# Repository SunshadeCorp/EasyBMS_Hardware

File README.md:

# EasyBMS_Hardware
PCB of the EasyBMS as an EAGLE project

Used EAGLE default design rules with one modification: under "Masks" in DRC settings, set "Limit" to 20mil to cover vias that have smaller drill size with solder mask.

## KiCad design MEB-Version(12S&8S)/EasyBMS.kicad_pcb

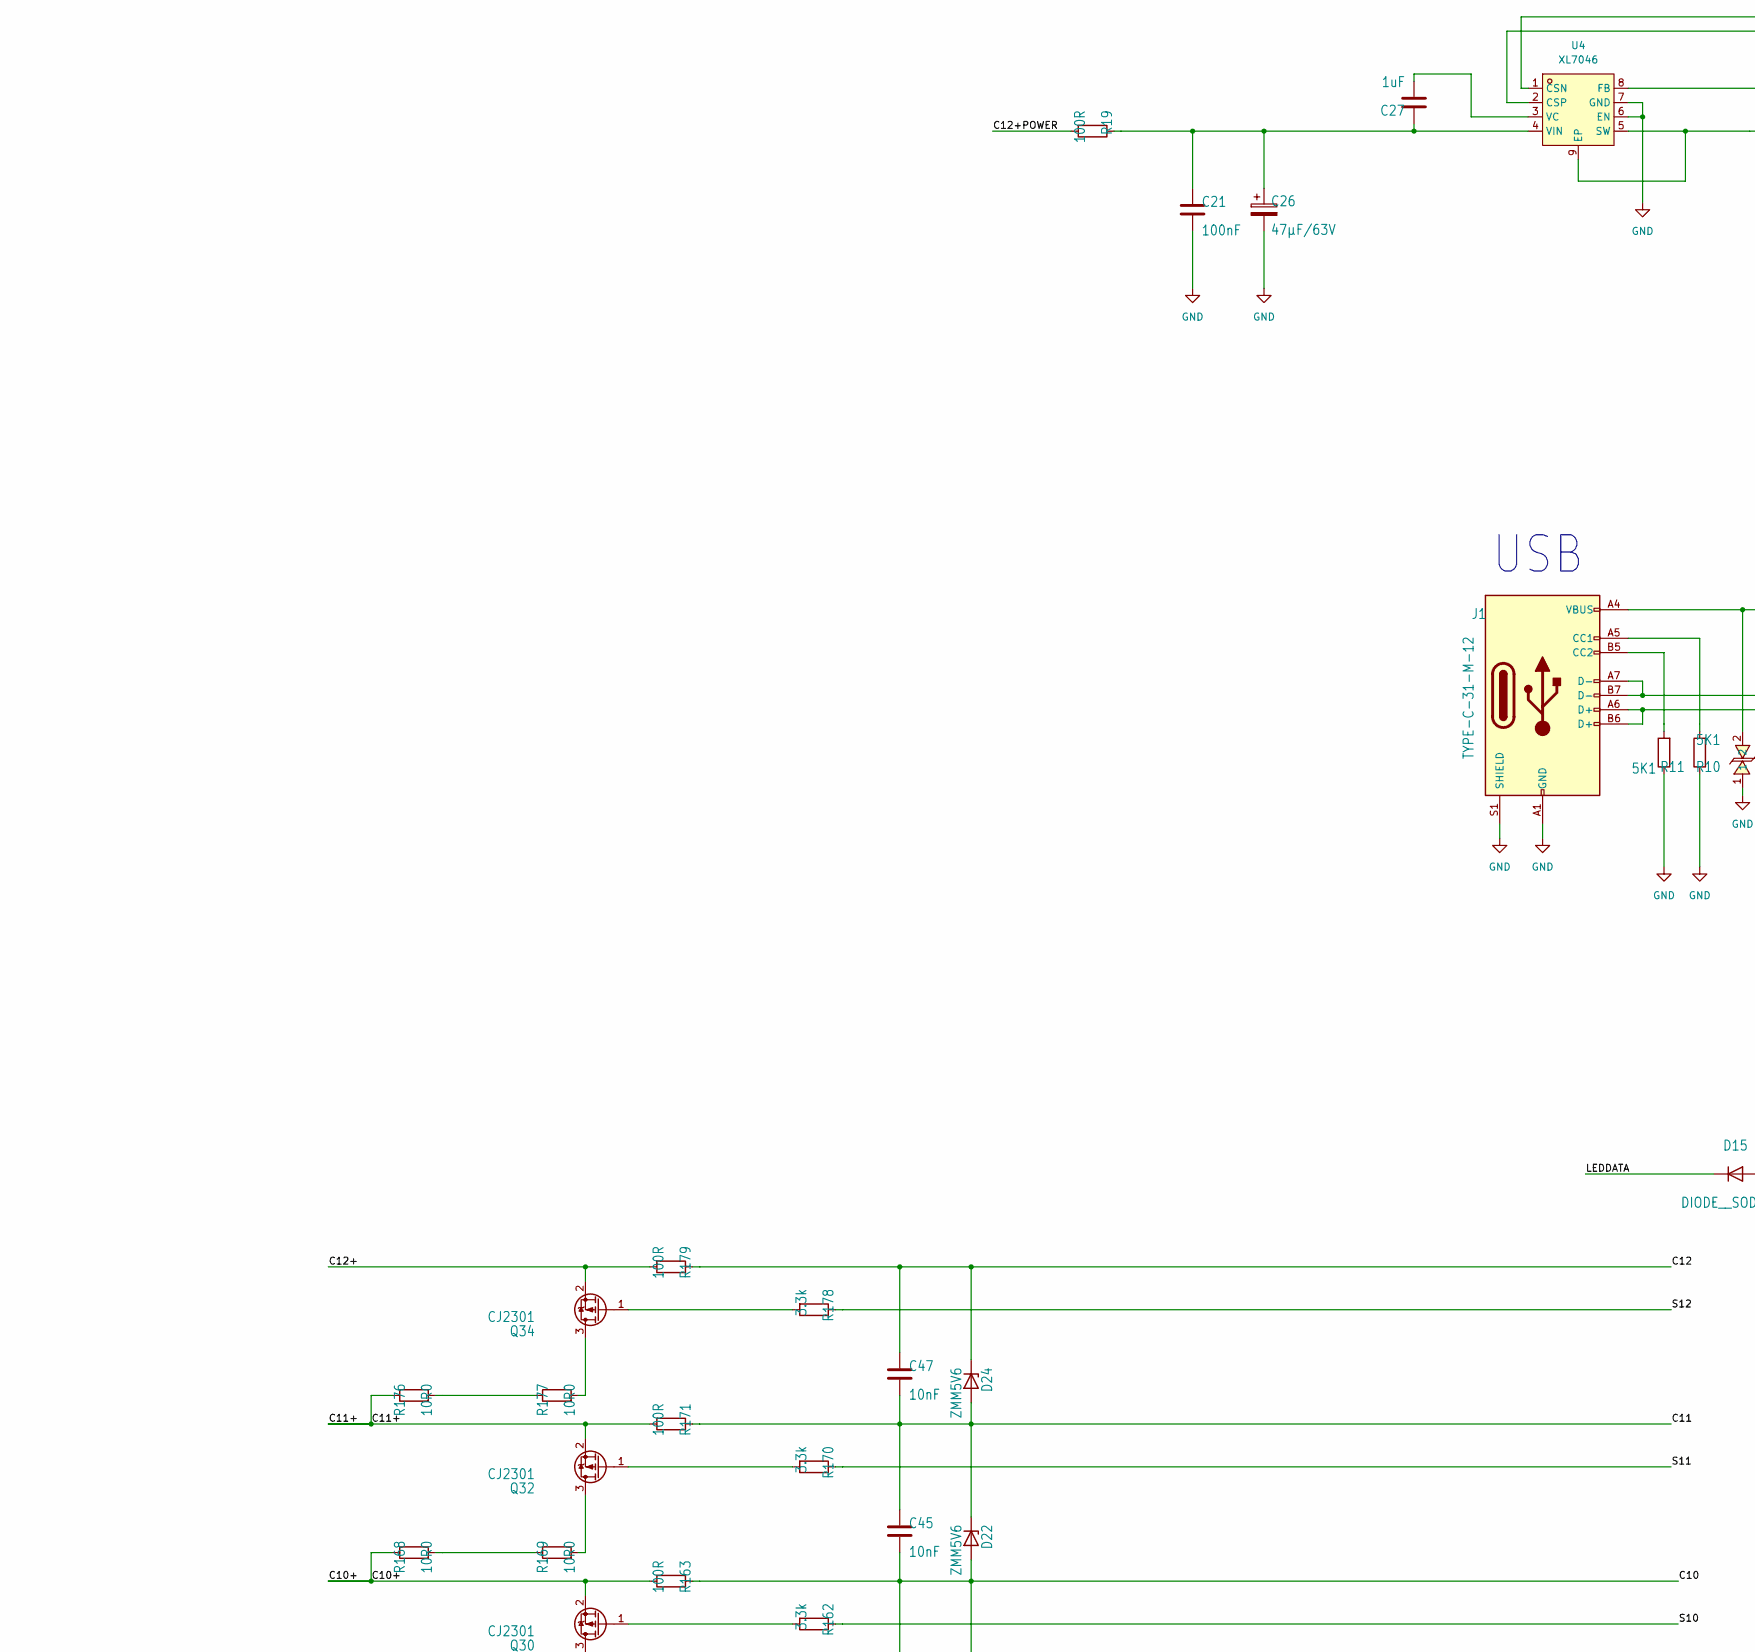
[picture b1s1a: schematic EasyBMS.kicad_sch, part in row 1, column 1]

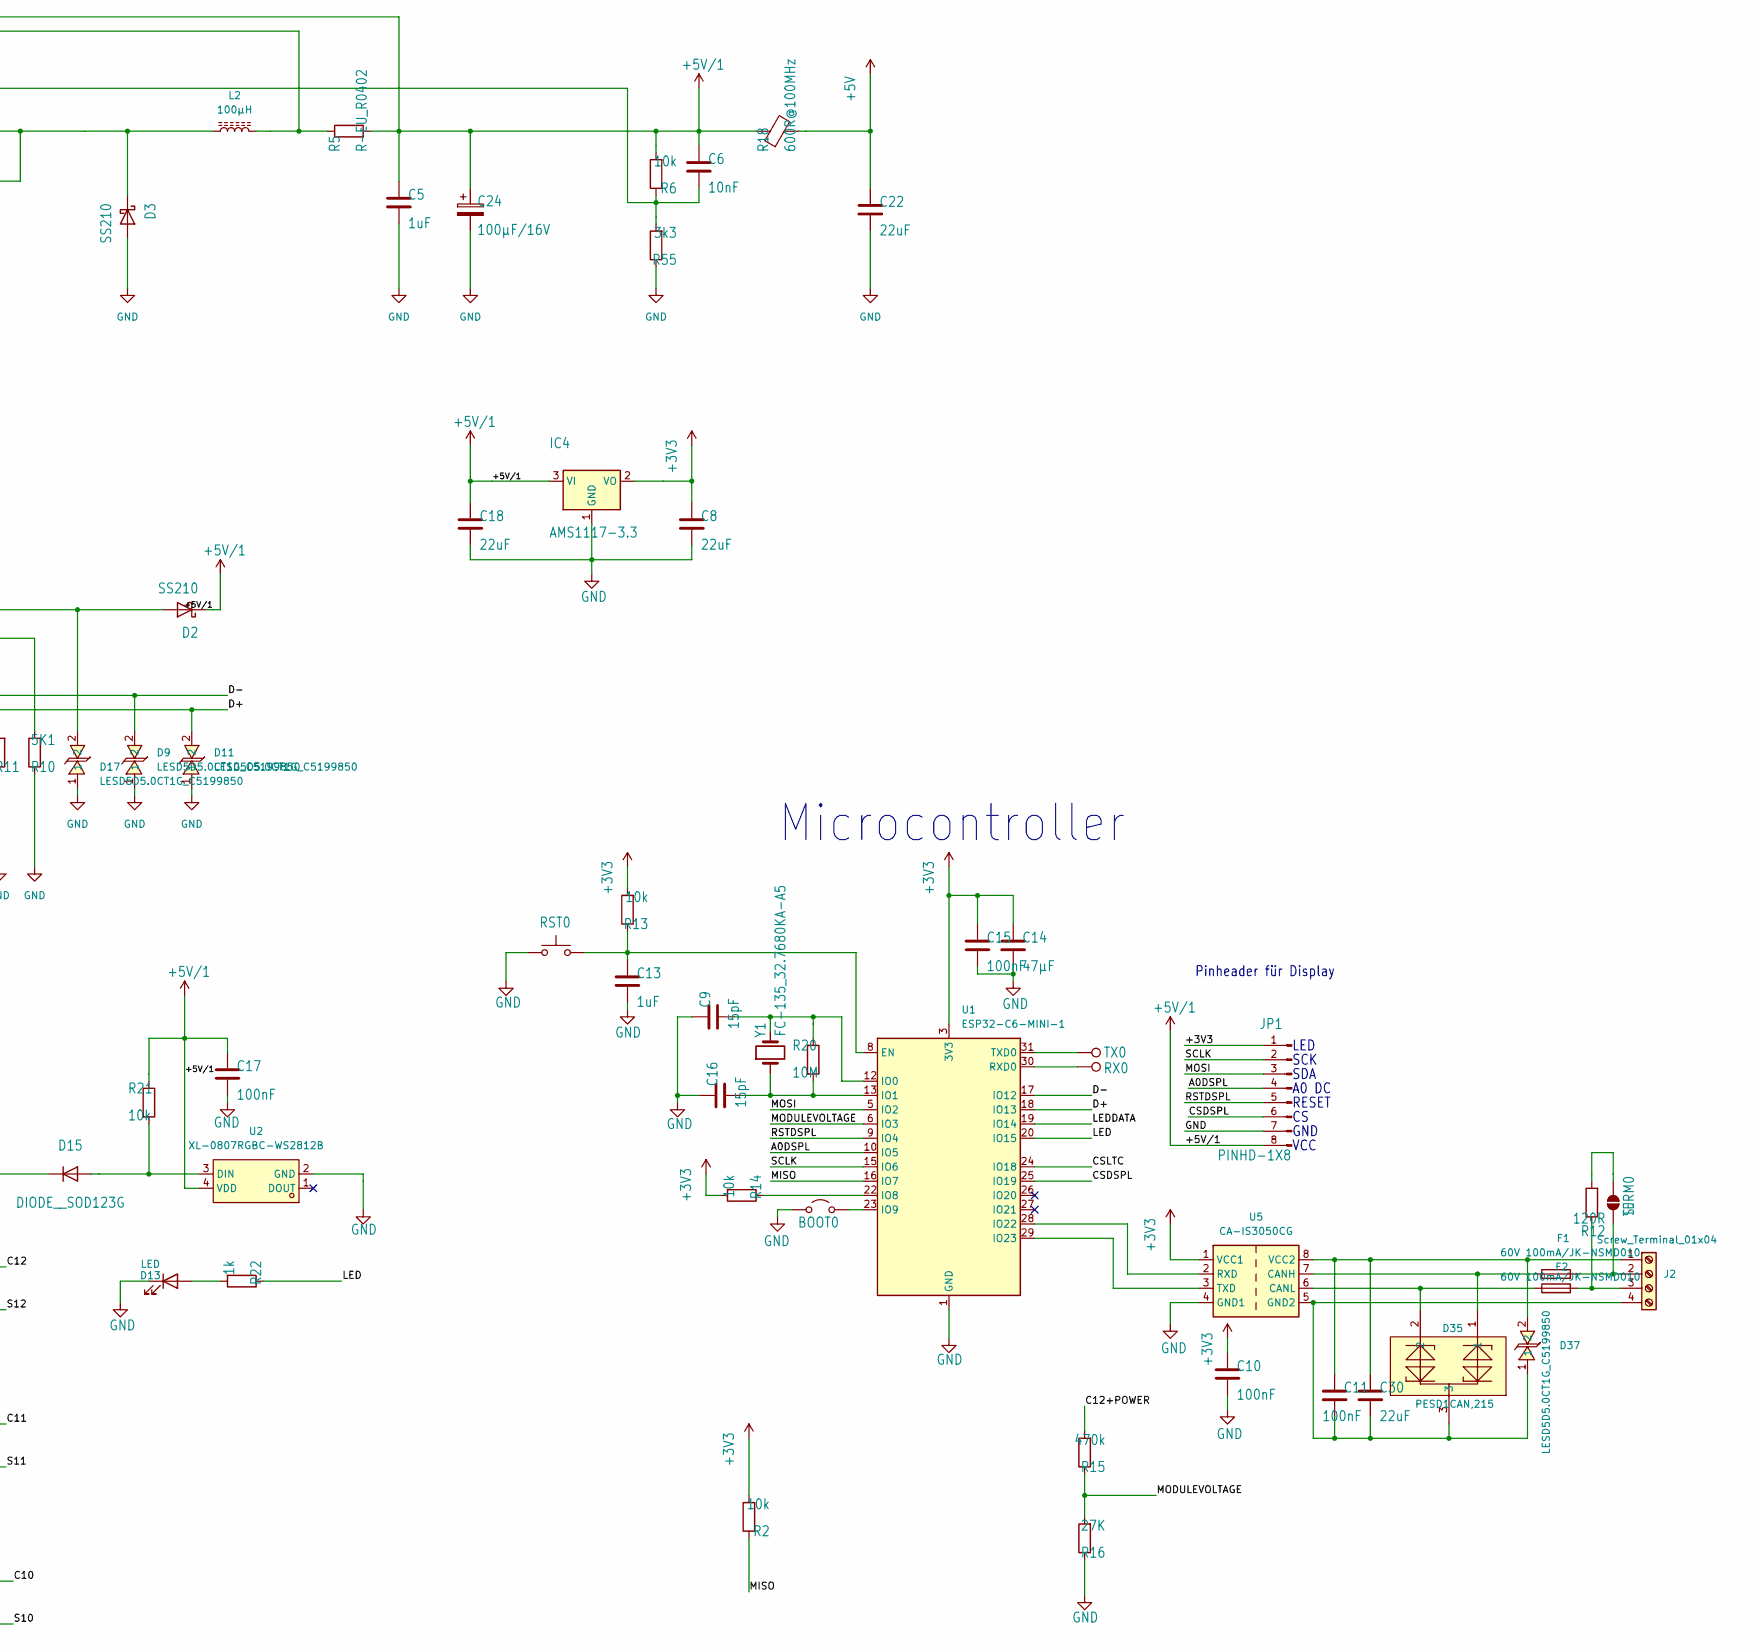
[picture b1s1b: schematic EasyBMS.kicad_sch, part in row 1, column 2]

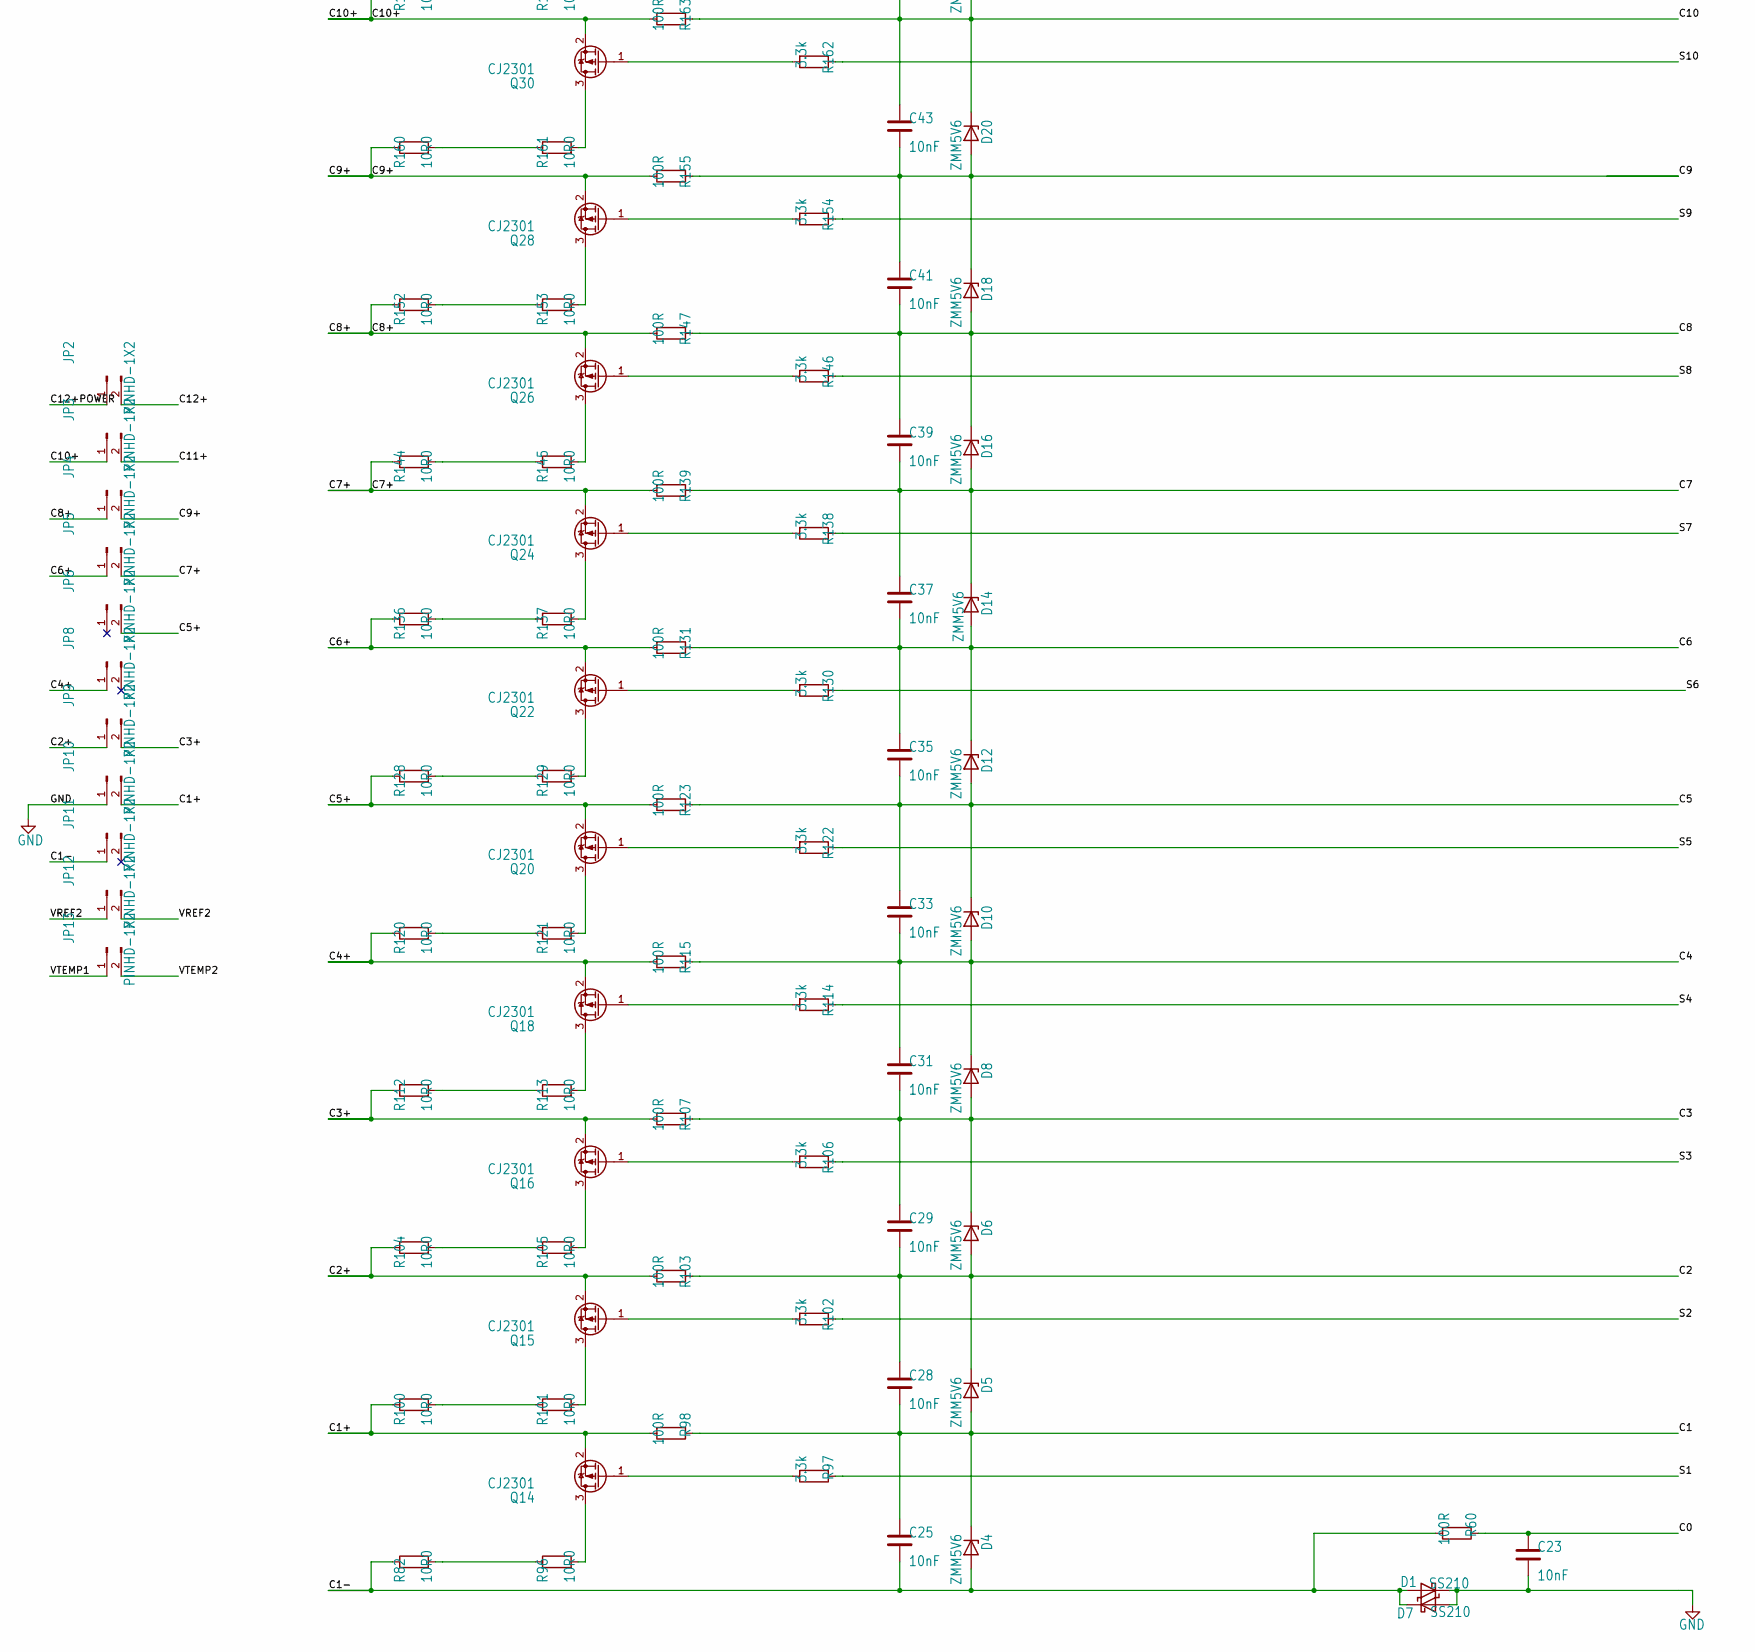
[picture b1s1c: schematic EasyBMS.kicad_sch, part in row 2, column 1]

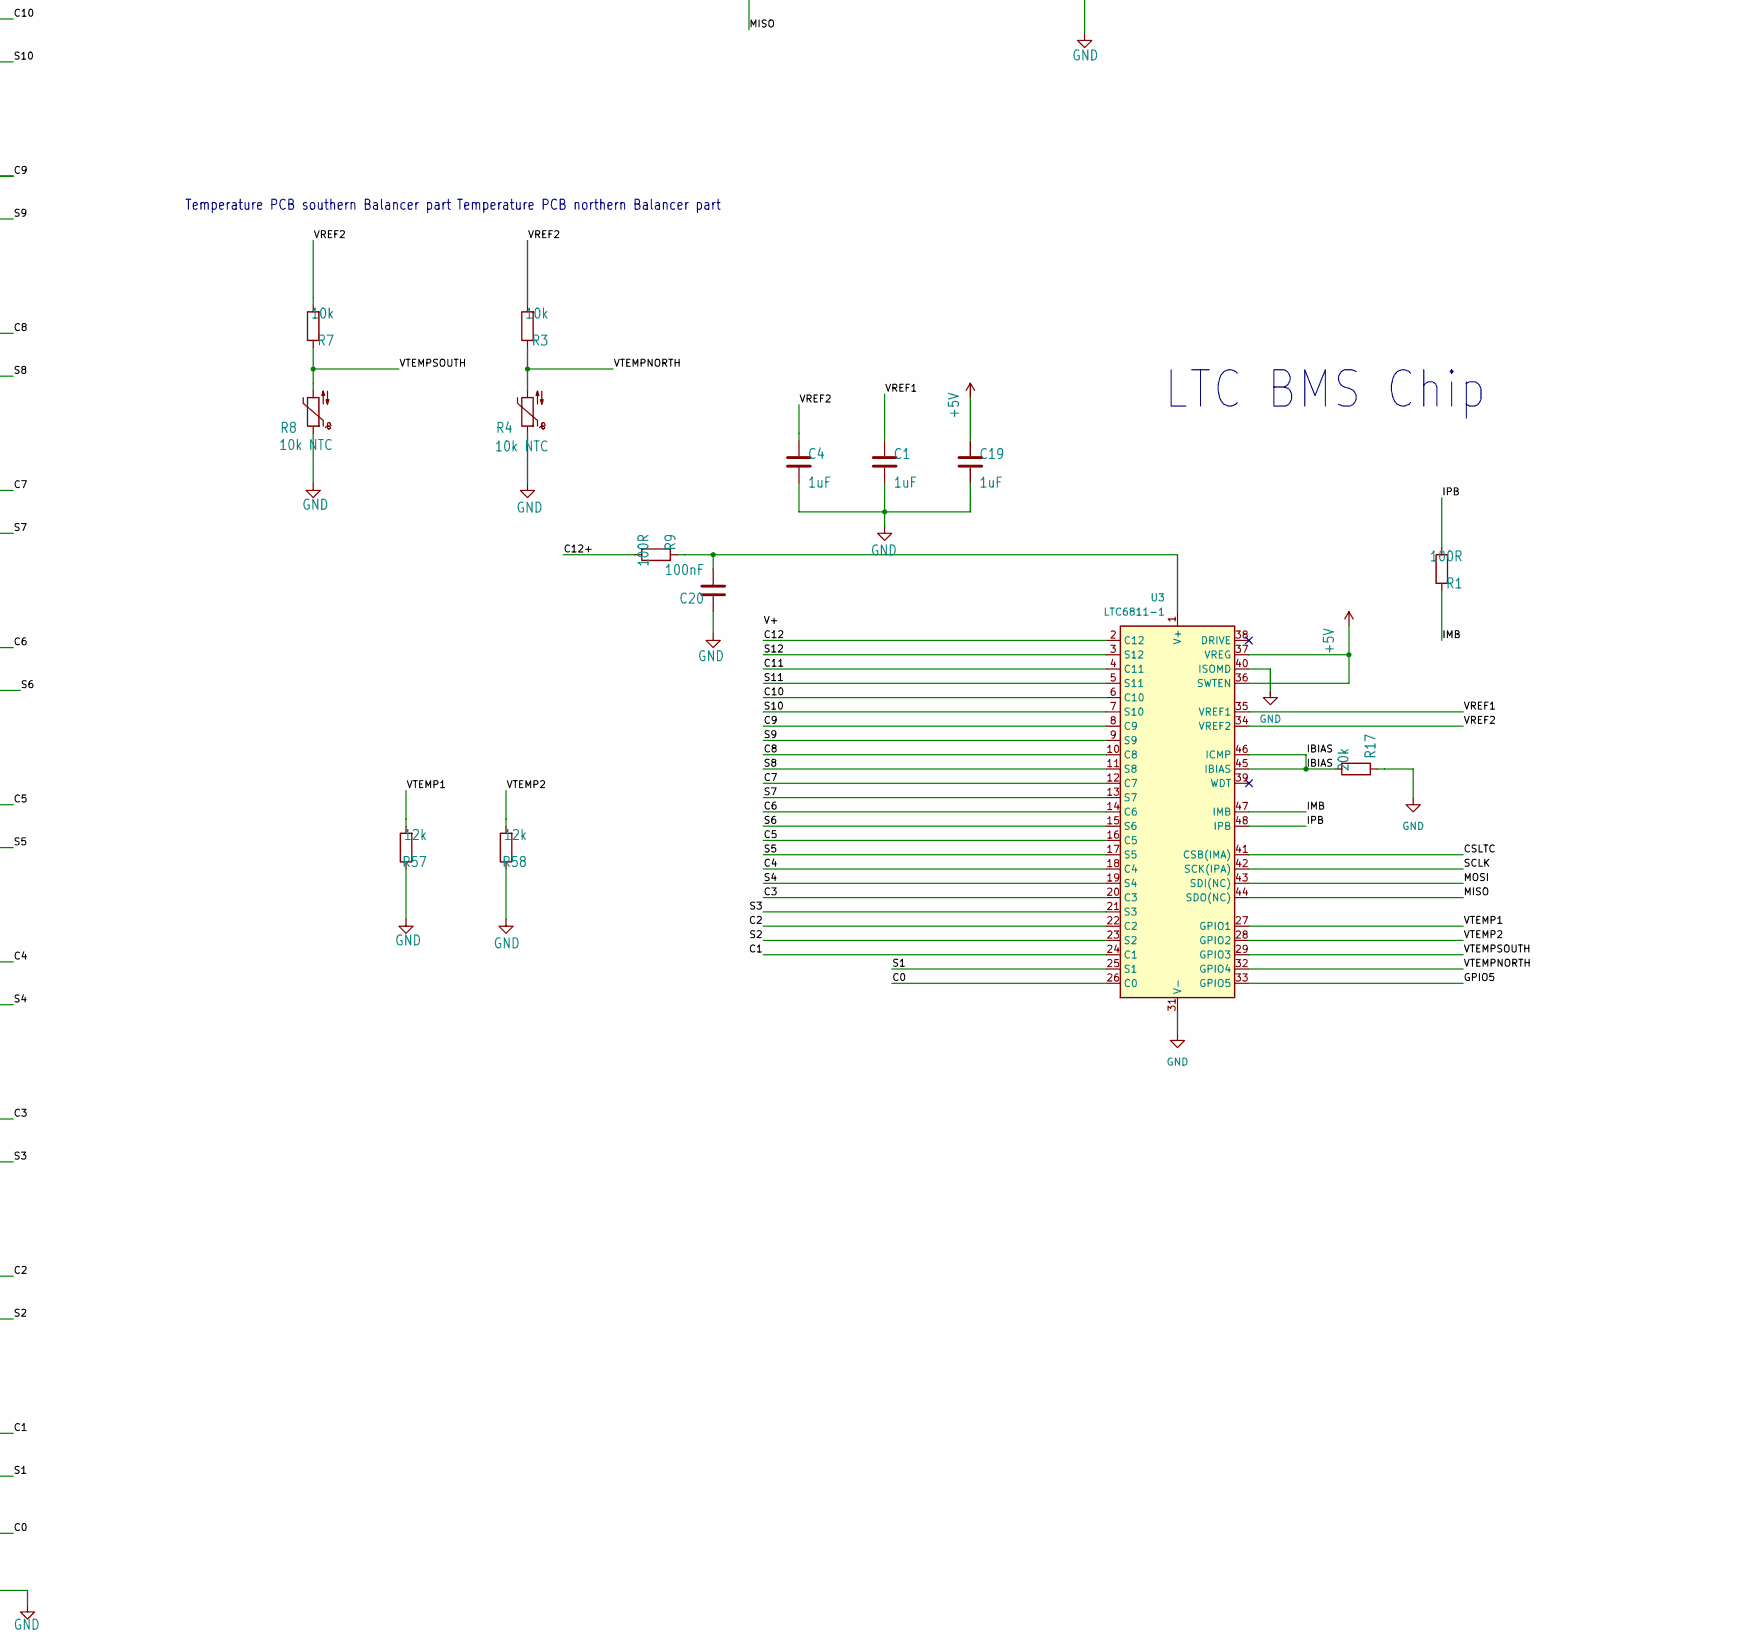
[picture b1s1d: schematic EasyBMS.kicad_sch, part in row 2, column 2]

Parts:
BOOT0: PINHD-1X2; PinHeader_1x02_P2.54mm_Vertical
C1, C4, C5, C13, C19: 1uF; C_0402_1005Metric; LCSC C52923
C6, C23, C25, C28, C29, C31, C33, C35, C37, C39, C41, C43, C45, C47: 10nF; C_0402_1005Metric; LCSC C15195
C8, C18, C22, C30: 22uF; C_0603_1608Metric; LCSC C59461
C9, C16: 15pF; C_0402_1005Metric; LCSC C1548
C10, C11, C15, C17: 100nF; C_0402_1005Metric; LCSC C307331
C14: 47µF; C_0805_2012Metric; LCSC C16780
C20, C21: 100nF; C_0805_2012Metric; LCSC C28233
C24: 100µF/16V; CP_Elec_6.3x5.4; LCSC C2887276
C26: 47µF/63V; CP_Elec_6.3x7.7; LCSC C2980165
C27: 1uF; C_0603_1608Metric; LCSC C15849
D1, D2, D3, D7: SS210; D_SMA; LCSC C14996
D4, D5, D6, D8, D10, D12, D14, D16, D18, D20, D22, D24: ZMM5V6; D_MiniMELF; LCSC C8062
D9, D11, D17, D37: LESD5D5.0CT1G_C5199850; D_SOD-523; LCSC Part C5199850
D13: LED; LED_0603_1608Metric; LCSC C2286
D15: DIODE__SOD123G; D_SOD-123; LCSC C81598
D35: PESD1CAN,215; SOT-23; LCSC Part C15771
F1, F2: 60V 100mA/JK-NSMD010; R_1206_3216Metric; LCSC C2830236
IC4: AMS1117-3.3; SOT-223-3_TabPin2; LCSC C6186
J1: TYPE-C-31-M-12; USB_C_Receptacle_HRO_TYPE-C-31-M-12; LCSC C2927039
J2: Screw_Terminal_01x04; TerminalBlock_TE_282834-4_1x04_P2.54mm_Horizontal
JP1: PINHD-1X8; PinHeader_1x08_P2.54mm_Vertical
JP2, JP3, JP4, JP5, JP6, JP8, JP9, JP10, JP11, JP12, JP13: PINHD-1X2; PinHeader_1x02_P2.54mm_Vertical; LCSC C3337950
L2: 100µH; IND-SMD_L7.8-W7.0-A; LCSC C2929443
Q14, Q15, Q16, Q18, Q20, Q22, Q24, Q26, Q28, Q30, Q32, Q34: CJ2301; SOT-23; LCSC C8547
R1: 100R; R_0603_1608Metric; LCSC C22775
R2, R6, R13, R14, R21: 10k; R_0402_1005Metric; LCSC C25744
R3, R7: 10k; R_0603_1608Metric; LCSC C25804
R4, R8: 10k NTC; R_0603_1608Metric; LCSC C13564
R5: R-EU_R0402; R_0402_1005Metric; LCSC C724022
R9, R60, R98, R103, R107, R115, R123, R131, R139, R147, R155, R163, R171, R179: 100R; R_0402_1005Metric; LCSC C25076
R10, R11: 5K1; R_0402_1005Metric; LCSC C25905
R12: 120R; R_0402_1005Metric; LCSC C25079
R15: 470k; R_0603_1608Metric; LCSC C23178
R16: 27K; R_0603_1608Metric; LCSC C22967
R17: 20k; R_0603_1608Metric; LCSC C4184
R18: 600R@100MHz; R_1206_3216Metric; LCSC C370100
R19: 100R; R_1206_3216Metric; LCSC C17901
R20: 10M; R_0402_1005Metric; LCSC C7250
R22: 1k; R_0402_1005Metric; LCSC C11702
R55: 3k3; R_0402_1005Metric; LCSC C25890
R57, R58: 12k; R_0402_1005Metric; LCSC C25752
R82, R96, R100, R101, R104, R105, R112, R113, R120, R121, R128, R129, R136, R137, R144, R145, R152, R153, R160, R161, R168, R169, R176, R177: 10R0; R_1206_3216Metric; LCSC C17903
R97, R102, R106, R114, R122, R130, R138, R146, R154, R162, R170, R178: 3.3k; R_0402_1005Metric; LCSC C25890
RST0: 10-XX; SW_PUSH_6mm
RX0: TPB2,54; TestPoint_Pad_D2.0mm
TERM0: SJ; SolderJumper-2_P1.3mm_Open_RoundedPad1.0x1.5mm
TX0: TPB2,54; TestPoint_Pad_D2.0mm
U1: ESP32-C6-MINI-1; LCSC C5736265
U2: XL-0807RGBC-WS2812B; LED-SMD_4P-L2.0-W1.8_XL-0807RGBC-WS2812B; LCSC Part C3646929
U3: LTC6811-1; SSOP-48_5.3x12.8mm_P0.5mm; LCSC C689566
U4: XL7046; ESOP-8_L4.9-W3.9-P1.27-LS6.0-TL-EP; LCSC Part C2843193
U5: CA-IS3050CG; SOIC-8_7.5x5.85mm_P1.27mm; LCSC C41383098
Y1: FC-135_32.7680KA-A5; FC-135R_L3.2-W1.5; LCSC C32346

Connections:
+3V3: C8.1, C10.1, C14.1, C15.1, IC4.2 (VO), JP1.1, R2.2, R13.2, R14.2, U1.3 (3V3), U5.1 (VCC1)
+5V: C19.1, C22.1, R18.2, U3.36 (SWTEN), U3.37 (VREG)
+5V/1: C5.1, C6.1, C17.1, C18.1, C24.1, D2.1 (K), IC4.3 (VI), JP1.8, R5.2, R6.2, R18.1, R21.1, U2.4 (VDD), U4.1 (CSN)
/A0DSPL: JP1.4, U1.10 (IO5)
/C0: C23.1, R60.1, U3.26 (C0)
/C1: C25.1, C28.2, D4.1 (K), D5.2 (A), R98.1, U3.24 (C1)
/C1+: JP10.2, Q14.2 (S), R98.2, R100.1
/C1-: C25.2, D1.1 (K), D4.2 (A), D7.2 (A), JP11.1, R60.2, R82.1
/C2: C28.1, C29.2, D5.1 (K), D6.2 (A), R103.1, U3.22 (C2)
/C2+: JP9.1, Q15.2 (S), R103.2, R104.1
/C3: C29.1, C31.2, D6.1 (K), D8.2 (A), R107.1, U3.20 (C3)
/C3+: JP9.2, Q16.2 (S), R107.2, R112.1
/C4: C31.1, C33.2, D8.1 (K), D10.2 (A), R115.1, U3.18 (C4)
/C4+: JP8.1, Q18.2 (S), R115.2, R120.1
/C5: C33.1, C35.2, D10.1 (K), D12.2 (A), R123.1, U3.16 (C5)
/C5+: JP6.2, Q20.2 (S), R123.2, R128.1
/C6: C35.1, C37.2, D12.1 (K), D14.2 (A), R131.1, U3.14 (C6)
/C6+: JP5.1, Q22.2 (S), R131.2, R136.1
/C7: C37.1, C39.2, D14.1 (K), D16.2 (A), R139.1, U3.12 (C7)
/C7+: JP5.2, Q24.2 (S), R139.2, R144.1
/C8: C39.1, C41.2, D16.1 (K), D18.2 (A), R147.1, U3.10 (C8)
/C8+: JP4.1, Q26.2 (S), R147.2, R152.1
/C9: C41.1, C43.2, D18.1 (K), D20.2 (A), R155.1, U3.8 (C9)
/C9+: JP4.2, Q28.2 (S), R155.2, R160.1
/C10: C43.1, C45.2, D20.1 (K), D22.2 (A), R163.1, U3.6 (C10)
/C10+: JP3.1, Q30.2 (S), R163.2, R168.1
/C11: C45.1, C47.2, D22.1 (K), D24.2 (A), R171.1, U3.4 (C11)
/C11+: JP3.2, Q32.2 (S), R171.2, R176.1
/C12: C47.1, D24.1 (K), R179.1, U3.2 (C12)
/C12+: JP2.2, Q34.2 (S), R9.2, R179.2
/C12+POWER: JP2.1, R15.2, R19.2
/CSDSPL: JP1.6, U1.25 (IO19)
/CSLTC: U1.24 (IO18), U3.41 (CSB(IMA))
/D+: D11.2, J1.A6 (D+), J1.B6 (D+), U1.18 (IO13)
/D-: D9.2, J1.A7 (D-), J1.B7 (D-), U1.17 (IO12)
/GPIO5: U3.33 (GPIO5)
/IBIAS: R17.2, U3.45 (IBIAS), U3.46 (ICMP)
/IMB: R1.1, U3.47 (IMB)
/IPB: R1.2, U3.48 (IPB)
/LED: R22.1, U1.20 (IO15)
/LEDDATA: D15.1 (K), U1.19 (IO14)
/MISO: R2.1, U1.16 (IO7), U3.44 (SDO(NC))
/MODULEVOLTAGE: R15.1, R16.2, U1.6 (IO3)
/MOSI: JP1.3, U1.5 (IO2), U3.43 (SDI(NC))
/RSTDSPL: JP1.5, U1.9 (IO4)
/S1: R97.1, U3.25 (S1)
/S2: R102.1, U3.23 (S2)
/S3: R106.1, U3.21 (S3)
/S4: R114.1, U3.19 (S4)
/S5: R122.1, U3.17 (S5)
/S6: R130.1, U3.15 (S6)
/S7: R138.1, U3.13 (S7)
/S8: R146.1, U3.11 (S8)
/S9: R154.1, U3.9 (S9)
/S10: R162.1, U3.7 (S10)
/S11: R170.1, U3.5 (S11)
/S12: R178.1, U3.3 (S12)
/SCLK: JP1.2, U1.15 (IO6), U3.42 (SCK(IPA))
/VREF1: C1.1, U3.35 (VREF1)
/VREF2: C4.1, JP12.1, JP12.2, R3.2, R7.2, U3.34 (VREF2)
/VTEMP1: JP13.1, R57.2, U3.27 (GPIO1)
/VTEMP2: JP13.2, R58.2, U3.28 (GPIO2)
/VTEMPNORTH: R3.1, R4.2, U3.32 (GPIO4)
/VTEMPSOUTH: R7.1, R8.2, U3.29 (GPIO3)
GND: BOOT0.1 (A), C1.2, C4.2, C5.2, C8.2, C9.1, C10.2, C13.2, C14.2, C15.2, C16.1, C17.2, C18.2, C19.2, C20.1, C21.2, C22.2, C23.2, C24.2, C26.2, D1.2 (A), D3.2 (A), D7.1 (K), D9.1, D11.1, D13.1 (K), D17.1, IC4.1 (GND), J1.A1 (GND), J1.A12 (GND), J1.B1 (GND), J1.B12 (GND), J1.S1 (SHIELD), JP1.7, JP10.1, R4.1, R8.1, R10.1, R11.1, R16.1, R17.1, R55.1, R57.1, R58.1, RST0.1, U1.1 (GND), U1.2 (GND), U1.11 (GND), U1.14 (GND), U1.36 (GND), U1.37 (GND), U1.38 (GND), U1.39 (GND), U1.40 (GND), U1.41 (GND), U1.42 (GND), U1.43 (GND), U1.44 (GND), U1.45 (GND), U1.46 (GND), U1.47 (GND), U1.48 (GND), U1.49 (GND), U1.50 (GND), U1.51 (GND), U1.52 (GND), U1.53 (GND), U2.2 (GND), U3.30 (V-), U3.31 (V-), U3.40 (ISOMD), U4.6 (EN), U4.7 (GND), U5.4 (GND1)
unnamed: BOOT0.2 (B), U1.23 (IO9)
unnamed: D2.2 (A), D17.2, J1.A4 (VBUS), J1.A9 (VBUS), J1.B4 (VBUS), J1.B9 (VBUS)
unnamed: D3.1 (K), L2.1, U4.5 (SW), U4.9 (EP)
unnamed: D13.2 (A), R22.2
unnamed: D15.2 (A), R21.2, U2.3 (DIN)
unnamed: J1.A5 (CC1), R10.2
unnamed: J1.B5 (CC2), R11.2
unnamed: C11.1, C30.1, D37.2, J2.1, U5.8 (VCC2)
unnamed: F1.2, J2.2, TERM0.1 (A)
unnamed: F2.2, J2.3, R12.1
unnamed: C11.2, C30.2, D35.3, D37.1, J2.4, U5.5 (GND2)
unnamed: Q14.1 (G), R97.2
unnamed: Q14.3 (D), R96.2
unnamed: Q15.3 (D), R101.2
unnamed: Q15.1 (G), R102.2
unnamed: Q16.3 (D), R105.2
unnamed: Q16.1 (G), R106.2
unnamed: Q18.3 (D), R113.2
unnamed: Q18.1 (G), R114.2
unnamed: Q20.3 (D), R121.2
unnamed: Q20.1 (G), R122.2
unnamed: Q22.1 (G), R130.2
unnamed: Q22.3 (D), R129.2
unnamed: Q24.3 (D), R137.2
unnamed: Q24.1 (G), R138.2
unnamed: Q26.1 (G), R146.2
unnamed: Q26.3 (D), R145.2
unnamed: Q28.1 (G), R154.2
unnamed: Q28.3 (D), R153.2
unnamed: Q30.3 (D), R161.2
unnamed: Q30.1 (G), R162.2
unnamed: Q32.3 (D), R169.2
unnamed: Q32.1 (G), R170.2
unnamed: Q34.3 (D), R177.2
unnamed: Q34.1 (G), R178.2
unnamed: R82.2, R96.1
unnamed: R100.2, R101.1
unnamed: R104.2, R105.1
unnamed: R112.2, R113.1
unnamed: R120.2, R121.1
unnamed: R128.2, R129.1
unnamed: R136.2, R137.1
unnamed: R144.2, R145.1
unnamed: R152.2, R153.1
unnamed: R160.2, R161.1
unnamed: R168.2, R169.1
unnamed: R176.2, R177.1
unnamed: R12.2, TERM0.2 (B)
unnamed: C13.1, R13.1, RST0.2, U1.8 (EN)
unnamed: C9.2, R20.1, U1.12 (IO0), Y1.2
unnamed: C16.2, R20.2, U1.13 (IO1), Y1.1
unnamed: R14.1, U1.22 (IO8)
unnamed: U1.28 (IO22), U5.2 (RXD)
unnamed: U1.29 (IO23), U5.3 (TXD)
unnamed: RX0.1, U1.30 (RXD0)
unnamed: TX0.1, U1.31 (TXD0)
unnamed: C20.2, R9.1, U3.1 (V+)
unnamed: L2.2, R5.1, U4.2 (CSP)
unnamed: C6.2, R6.1, R55.2, U4.8 (FB)
unnamed: C27.2, U4.3 (VC)
unnamed: C21.1, C26.1, C27.1, R19.1, U4.4 (VIN)
unnamed: D35.1, F1.1, U5.7 (CANH)
unnamed: D35.2, F2.1, U5.6 (CANL)

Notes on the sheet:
Temperature PCB southern Balancer part
Pinheader für Display
USB
LED
LTC BMS Chip
GND
Temperature PCB northern Balancer part
SDA
SCK
RESET
VCC
Microcontroller
A0 DC

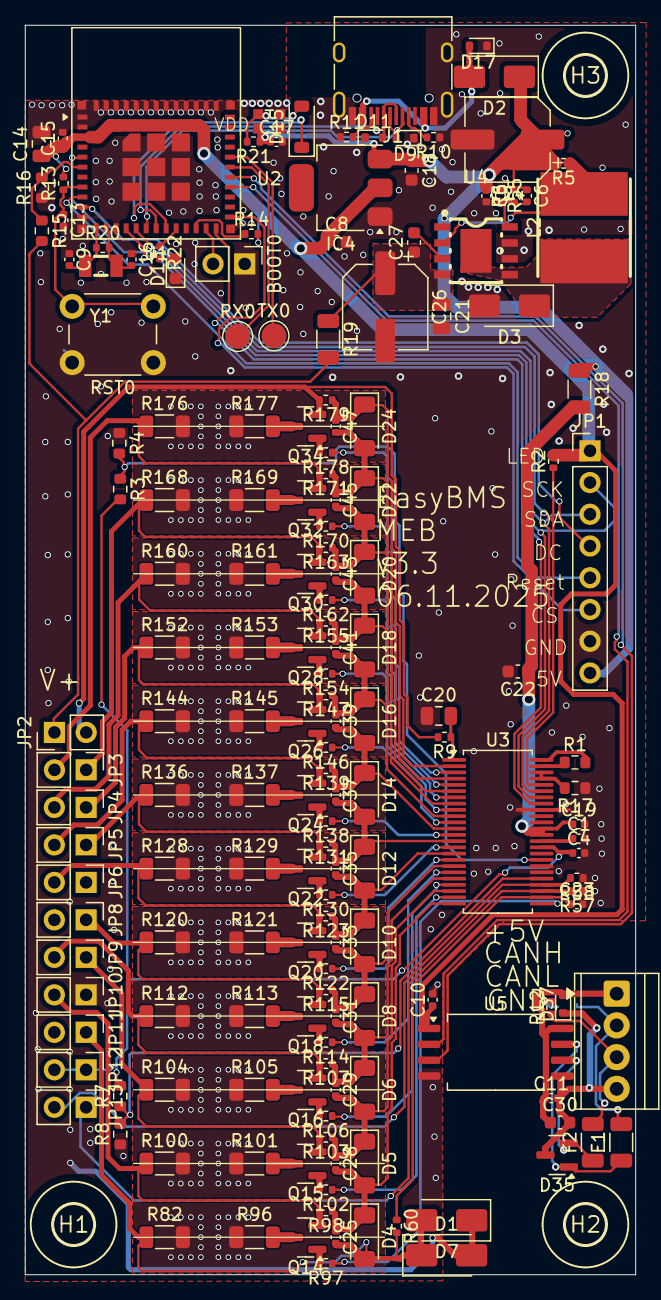
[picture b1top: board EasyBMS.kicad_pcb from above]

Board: 2 copper layers, 48.8 x 100.0 mm, 176 parts (1 on the bottom side), 127 nets.

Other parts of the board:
H1, H2, H3: MOUNT-HOLE3.2; 3,2_237

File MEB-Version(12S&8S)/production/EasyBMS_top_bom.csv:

Comment,Designator,Footprint,LCSC Part #
1uF,C2 C24 C26 D4 D5 D6 D8 D10 D12 D14 D16 D18 D20 D22 D24 R5 TERM C1 C4 C5 C7 C13 C19,C0402,
1uF,C27,C0603,
3.3k,R97 R102 R106 R114 R122 R130 R138 R146 R154 R162 R170 R178,R0402,
3k3,R55,R0402,
5K1,R10 R11,R0402,
10M,R20,R0402,
10R0,R82 R96 R100 R101 R104 R105 R112 R113 R120 R121 R128 R129 R136 R137 R144 R145 R152 R153 R160 R161 R168 R169 R176 R177,R1206,
10k,R2,R0402,
10k,R3,R0603,
10k,R6,R0402,
10k,R7,R0603,
10k,R13 R14 R21,R0402,
10nF,C6 C23 C25 C28 C29 C31 C33 C35 C37 C39 C41 C43 C45 C47,C0402,
12k,R57 R58,R0402,
15pF,C9 C16,C0402,
20k,R17,R0603,
22uF,C8,C0603,
27K,R16,R0603,
47uF,C12,C1206,
47uF,C14,C0805,
100R,R1,R0603,
100R,R9,R0402,
100R,R19,R1206,
100R,R60 R98 R103 R107 R115 R123 R131 R139 R147 R155 R163 R171 R179,R0402,
100nF,C3 C10 C11 C15 C17,C0402,
100nF,C20 C21,C0805,
120R,R12,R0402,
470k,R15,R0603,
AMS1117-3.3,IC4,SOT223,C6186
C8547,Q14 Q15 Q16 Q18 Q20 Q22 Q24 Q26 Q28 Q30 Q32 Q34,PG-SOT-23,
C13564,R4 R8,R0603,
C370100,R18 R59,R1206,
C2929443,L1,CY75-100UH,C2929443
DIODE_1N4448W-TP_SOD123G,D15,SOD3715X135,C81598
ESP32-C6-MINI-1-N4,U1,XCVR_ESP32-C6-MINI-1-N4,C5736265
FC-135_32.7680KA-A5,Y1,FC135327680KAA5,C32346
ISO1042DWV,IC3,SOIC127P1150X280-8N,C528763
LESD5D5.0CT1G,D9 D11 D13,SOD523,C5199850
LTC6811IG-1#PBF,IC2,SOP50P780X200-48N,
SS210,D1 D2 D3 D7,DO214AC,C14996
TPB2 54,RX,B2 54,
TPB2 54,TX,B2 54,
TYPE-C-31-M-12,J1,HRO_TYPE-C-31-M-12,C2927039
XL-1615RGBC-WS2812B,LED2,XL-1615RGBC-WS2812B,C5349954
XL7046,IC1,SOIC127P600X170-9N,C2843193

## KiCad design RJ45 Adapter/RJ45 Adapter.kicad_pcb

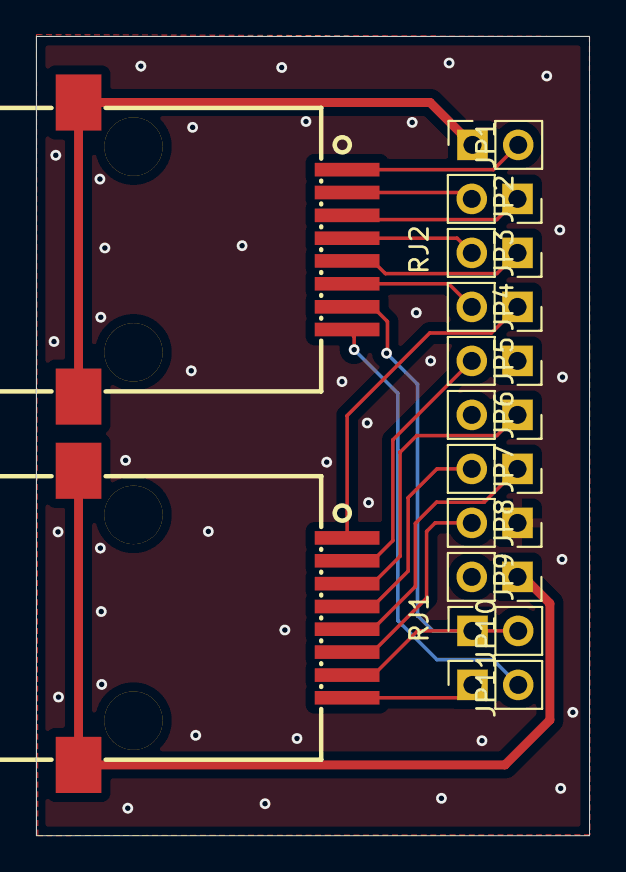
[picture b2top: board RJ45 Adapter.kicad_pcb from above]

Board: 2 copper layers, 30.7 x 44.4 mm, 13 parts (0 on the bottom side), 17 nets.

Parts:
JP1, JP2, JP3, JP4, JP5, JP6, JP7, JP8, JP9, JP10, JP11: PINHD-1X2; PinSocket_1x02_P2.54mm_Vertical
RJ1, RJ2: MJ88-B211-JRS3; RJ45-SMD_HELING_MJ88-B211-JRS3

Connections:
/C1+: JP8.2, RJ1.6
/C1-: JP9.1, RJ1.9, RJ1.10
/C2+: JP7.1, RJ1.5
/C3+: JP7.2, RJ1.4
/C4+: JP6.1, RJ1.3
/C5+: JP5.2, RJ1.2
/C6+: JP4.1, RJ1.1
/C7+: JP4.2, RJ2.6
/C8+: JP3.1, RJ2.5
/C9+: JP3.2, RJ2.4
/C10+: JP2.1, RJ2.3
/C11+: JP2.2, RJ2.2
/C12+: JP1.2, RJ2.1
/C12+POWER: JP1.1, RJ2.9, RJ2.10
/VREF2: JP10.1, JP10.2, RJ1.7, RJ2.7
/VTEMP1: JP11.1, RJ1.8
/VTEMP2: JP11.2, RJ2.8

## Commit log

2021-07-05 Initial upload of existing files
    debugversion with bug in supply voltage
2021-07-05 supply voltage bug removed
2021-07-09 minimize board size to 100x32
2021-07-09 size changed to 100x49
2021-07-14 transistor changed to the type from example BSS308
2021-07-14 shortconnection pinable between the C ports for emtpy cells
2021-07-18 some caps got new values
2021-07-18 MOSFETS changed to a available Type
2021-07-19 layouted
2021-07-19 layouted and release candidate
2021-07-19 parts placement and routes optimized
2021-07-19 add vias, fix with battery measurement
2021-07-20 gerber files generated
2021-07-20 assembly files added
2021-08-27 added jumper for connecting any cell to V+ reworked jumper on C pins for easier handling
2021-08-29 IC adapter added
2021-08-29 IC adapter layouted
2021-08-30 new routing of small IC Adapter
2021-08-30 current sensor board added
2021-08-30 current sensor got some r and c
2021-08-30 current sensor layouted
2021-08-31 isolation distance improved
2021-08-31 cleaning
2021-08-31 new 2x20 header used
2021-08-31 positioning
2021-08-31 extension ports added
2021-08-31 new extension board design used
2021-09-01 current sensor board routed
2021-09-02 nothing changed
2021-09-02 replacing some parts in the layout
2021-09-02 VREF1 set to unused, only VREF2 is used now
2021-09-02 library for 50A current sernsor ACS758 added
2021-09-02 sensor changed to ACS758
2021-09-02 sensor ACS758 layouted
2021-09-02 ground plate added
2021-09-02 thermal deactivated
2021-09-02 restructured layout
2021-09-02 current sensor moved to microversion
2021-09-02 current sensor added
2021-09-02 new footprint for current sensor added
2021-09-02 layout finished
2021-09-03 Order done Current Sensor Multi
2021-09-03 layout changes
2021-09-04 manufacturing data produced with a multi design
2021-09-06 GPIO Adapter board added
2021-09-06 GPIO got terminal blocks
2021-09-07 GPIO board ready for manufactoring
2021-09-10 renaming current sensor and adding voltage measurement module
2021-09-10 voltage module layouted
2021-09-10 voltage module layout changed
2021-09-12 multiversion created
2021-09-12 multiversion finished
2021-09-30 high voltage measurement
2021-09-30 multi made to 4x boards
2021-10-01 new branch for meb
2021-10-10 IC adapter is a 4x multiboard now
2021-10-11 MEB parts placed
2021-10-11 new branch for sensor modules, deleted other files
2021-10-11 moved current sensor EGALE libs to sensors branch
2021-10-27 review of layout #1
2021-10-29 gerber and assembly files generated
2021-11-23 8s layout is finished, its okay
2021-11-24 ESP8266 moved 4mm to the upper border
2021-11-25 review: ready to manufacture
2021-11-25 fixed bug with GND from module and rerouted some traces
2021-11-25 fixed bug with GND from module
2021-12-03 deleted Testbench files, have its own branch
2021-12-08 fixed GND plane to thin at one place as stated by JLC
2021-12-08 VIA moved to prevent thin GND plane
2021-12-08 trace moved for better routing
2021-12-08 VIA moved
2021-12-13 revision tag added
2021-12-13 dimensions corrected
2021-12-13 coordinates fixed
2021-12-13 gerber files generated for 12s
2021-12-13 multiboards added
2022-01-10 moved ESP 4mm to top edge of board similar to 8S version
2022-01-18 minor changes to layout
2022-04-01 new folder structure
2022-04-01 add 2x20 Pin IC-Adapter
2022-04-01 add 8S version on MEB branch
2022-04-01 apply new folder structure
2022-04-01 apply new folder structure, add 2x1x24 Pin IC-Adapter
2022-04-12 cover VIAS with solder mask, new Panel-design and production data needed
2022-04-12 new version number
2022-04-12 cover VAS with solder mask
2022-04-12 update README with used design rules
2022-04-12 cover VIAS with solder mask
2022-04-13 removed diode, connected V+ and C12+, GND and BAT-, improved routing for C1 - C4
2022-07-09 SMD pinheader added as a part
2022-07-09 SMD pinheader swaped but not placed
2022-07-09 traced ripped up
2022-07-19 IC directly placed on base board, no tracing done
2022-07-19 Routing nearly done, difficult lines done
2022-07-19 everything routed, no DRC errors
2022-07-19 cosmetics
2022-07-25 Bugfix of SPI MISO pullup and Bat C1- connection
2022-07-26 new branch for LTC68xx-1 chip, small changes on base board
2022-12-04 symbol of 6811-1 replaced to a original -1 symbol
2023-01-20 add schematic for dc converter design
2023-01-20 some traces removed
2023-01-20 new parts placed inside of the board for a first cost estimation on jlc
2023-01-20 layout with integrated dc/dc is ready, changed input capacitor to a larger one
2023-01-20 moved some parts a bit to solve collisions
2023-01-20 moved parts a bit further and changed footprint slightly
2023-01-20 production files generated and ordered
2023-01-20 added 3D models for lm2596 and 470uF cap and generate 3D files for EasyBMS board
2023-02-25 added 100R in serial of DCDC input to limit rush in current, separate V+ wires used
2023-02-25 GND seperated in GND2 and GND
2023-02-27 reviewed and new pcb version
2023-02-28 checked and ready manufacture
2023-03-25 documentation of 1.8inch display added
2023-03-25 example added
2023-03-25 Use correct display configuration in display example code
2023-03-25 display pins pic
2023-03-26 documentation file filled
2023-03-26 comments to Digital pins added
2023-03-26 pinheader for display added
2023-04-04 moved display connector
2023-04-04 thermals added for THT pins
2023-04-04 pin distance battery connector changed to 2.7mm
2023-04-04 production files added, ready to manufacture
2023-04-24 level shifter base design added
2023-04-24 paneled boards removed
2023-04-25 removed deprecated files
2023-05-04 level shifter 3,3V<>5V added
2023-05-08 production data generated, ready to order
2023-05-08 bug on 2 LEDs removed, new production files generated
2023-07-02 level shifter removed
2024-02-03 design blocks added
2024-02-03 obsolet file deleted
2024-02-03 New controller added as part
2024-02-03 design block updated to more copper and Zener added
2024-02-03 dummy IC added
2024-02-03 new parts for DC DC added
2024-02-03 XL7046 properly added
2024-02-03 balancer path reworked
2024-02-03 balancer path reworked2
2024-02-04 USB-C port added
2024-02-15 dbl reworked, more compact
2024-02-15 placing started
2024-02-16 basic routing done. DCDC next step
2024-02-16 2 Temperature sensors added
2024-02-16 RGB LED added
2024-02-26 DCDC routed
2024-09-11 replaced DCDC and possibly fixed dead LTCs
2024-09-17 update gitignore
2024-09-17 placed and routed new design, ready for review
2024-09-19 remove old conflicting production file
2024-09-19 moved files in common folder structure
2024-09-24 renamed design blocks folder as EAGLE names it
2024-09-24 add libraries folder with ESP32-C6 lib and change ESP32-S3 to ESP32-C6 MCU
2025-02-21 add lib for isolated CAN-Transceiver
2025-02-21 new version v3.0 review layout, change some parts and add isolated CAN-transceiver
2025-02-22 add STEP files and new lib for 32khz crystal
2025-02-22 add recommended aux parts for ESP module
2025-02-22 new production data
2025-02-24 change some parts to basic parts, add USB protection
2025-02-24 new production files
2025-02-24 change LED pixel circuit as in C6 Devkit
2025-02-28 check in KiCAD files after import
2025-02-28 parts selected
2025-03-01 new Footprint to change to basic parts
2025-03-05 update imported libraries: fix broken pads
2025-03-05 change to correct footprints, add LCSC numbers to schematic
2025-03-12 add lib for dc/dc choke
2025-03-12 change DRC rules to JLC capabilities and solve DRC errors
2025-04-15 fixed wrong footprints and symbols, connect 3d models with footprints
2025-05-07 some cosmetics in schematic
2025-05-07 check in schematic of new dual version for two modules on one PCB
2025-05-08 new grounding with one common ground
2025-05-14 add RJ45 to MEB adapter to connect battery over RJ45
2025-05-14 schematic improvements, parts changed, layout progress
2025-05-18 add EasyEDA2KiCad lib with JLC parts
2025-05-18 schematic and layout finalized, production data generated
2025-05-19 add ESD protection to CAN, more clearance on high voltage diff
2025-09-24 changed settings for jlc parts
2025-09-30 new RGB LED and additional simple red LED
2025-09-30 changed RGB LED and new simple red LED
2025-11-06 replace old imported symbols and footprints with kicad ones
